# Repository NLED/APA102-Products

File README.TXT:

THERE IS NO WARRANTY FOR THE PROGRAM, TO THE EXTENT PERMITTED BY APPLICABLE LAW. 
EXCEPT WHEN OTHERWISE STATED IN WRITING THE COPYRIGHT HOLDERS AND/OR OTHER PARTIES 
PROVIDE THE PROGRAM “AS IS” WITHOUT WARRANTY OF ANY KIND, EITHER EXPRESSED OR IMPLIED,
INCLUDING, BUT NOT LIMITED TO, THE IMPLIED WARRANTIES OF MERCHANTABILITY AND FITNESS 
FOR A PARTICULAR PURPOSE. THE ENTIRE RISK AS TO THE QUALITY AND PERFORMANCE OF THE 
PROGRAM IS WITH YOU. SHOULD THE PROGRAM PROVE DEFECTIVE, YOU ASSUME THE COST OF ALL 
NECESSARY SERVICING, REPAIR OR CORRECTION.

 Original Author: Jeffrey Nygaard
 Company: Northern Lights Electronic Design, LLC
 Date: March 5, 2018
 Contact: JNygaard@NLEDshop.com
 Copyright© 2017 by Northern Lights Electronic Design, LLC. All Rights Reserved
 
;=============          www.NLEDShop.com/apa102products           ============
;=============     www.NorthernLightsElectronicDesign.com       ============

This work is licensed under a Attribution-NonCommercial 4.0 International (CC BY-NC 4.0)
https://creativecommons.org/licenses/by-nc/4.0/legalcode

Free to use for personal use, but please attribute the original author.

Commercial licenses versions are available for a donation of any amount. Contact JNygaard@NLEDshop.com for details.

================================================================================================================

Ready-made devices are available for purchase, and large batch manufacturing of any device can be requested.
Please see the webpage www.NLEDShop.com/pixelproducts

NLED is available for custom design and manufacturing, please contact via phone or email to discuss your project.

================================================================================================================

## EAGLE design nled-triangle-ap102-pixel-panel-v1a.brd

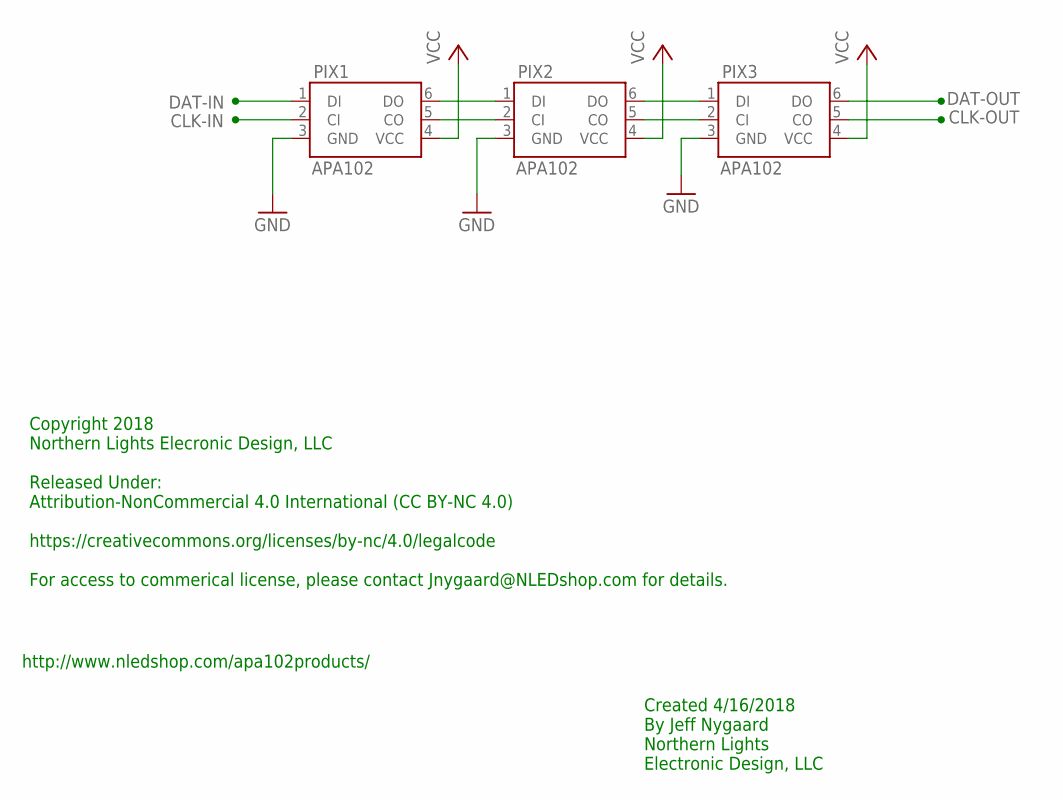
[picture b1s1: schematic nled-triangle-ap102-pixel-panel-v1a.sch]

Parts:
PIX1, PIX2, PIX3: APA102

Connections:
CLK-IN: PIX1.2 (CI)
CLK-OUT: PIX3.5 (CO)
DAT-IN: PIX1.1 (DI)
DAT-OUT: PIX3.6 (DO)
GND: PIX1.3 (GND), PIX2.3 (GND), PIX3.3 (GND)
unnamed: PIX1.6 (DO), PIX2.1 (DI)
unnamed: PIX1.5 (CO), PIX2.2 (CI)
unnamed: PIX2.6 (DO), PIX3.1 (DI)
unnamed: PIX2.5 (CO), PIX3.2 (CI)
VCC: PIX1.4 (VCC), PIX2.4 (VCC), PIX3.4 (VCC)

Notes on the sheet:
Copyright 2018 Northern Lights Elecronic Design, LLC Released Under: Attribution-NonCommercial 4.0 International (CC BY-NC 4.0) https://creativecommons.org/licenses/by-nc/4.0/legalcode For access to commerical license, please contact Jnygaard@NLEDshop.com for details.
Created 4/16/2018 By Jeff Nygaard Northern Lights Electronic Design, LLC
http://www.nledshop.com/apa102products/

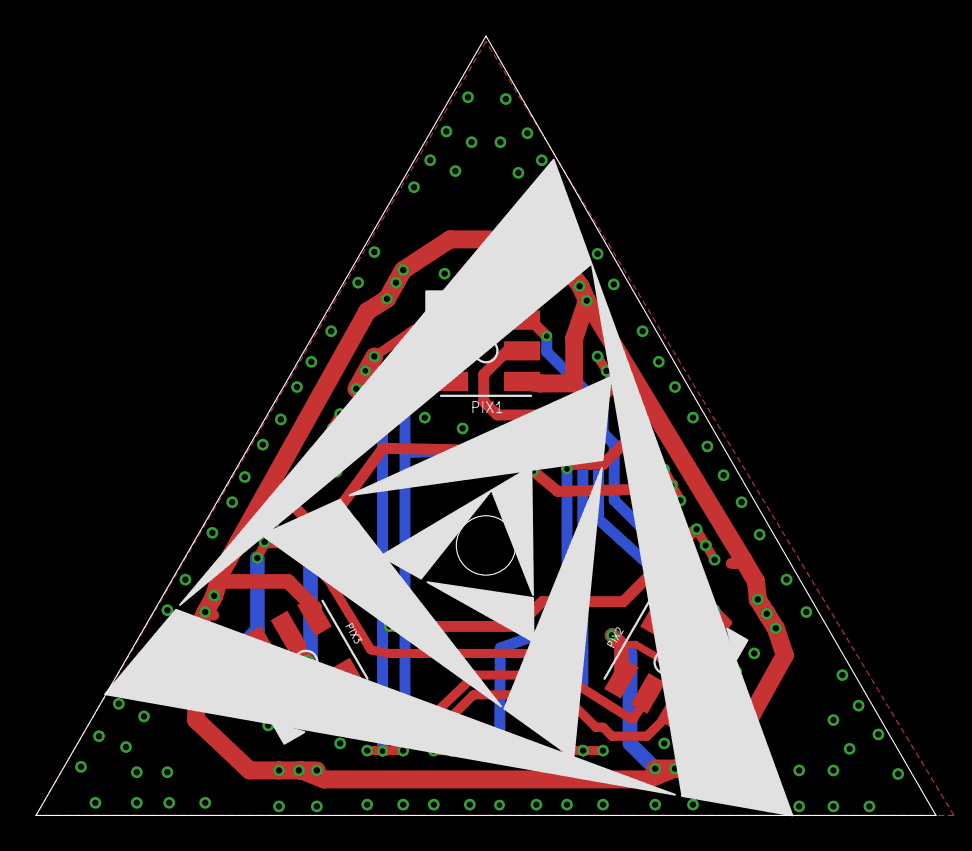
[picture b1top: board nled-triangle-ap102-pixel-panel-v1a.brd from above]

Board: 2 copper layers, 50.0 x 43.3 mm, 3 parts (0 on the bottom side), 6 nets.

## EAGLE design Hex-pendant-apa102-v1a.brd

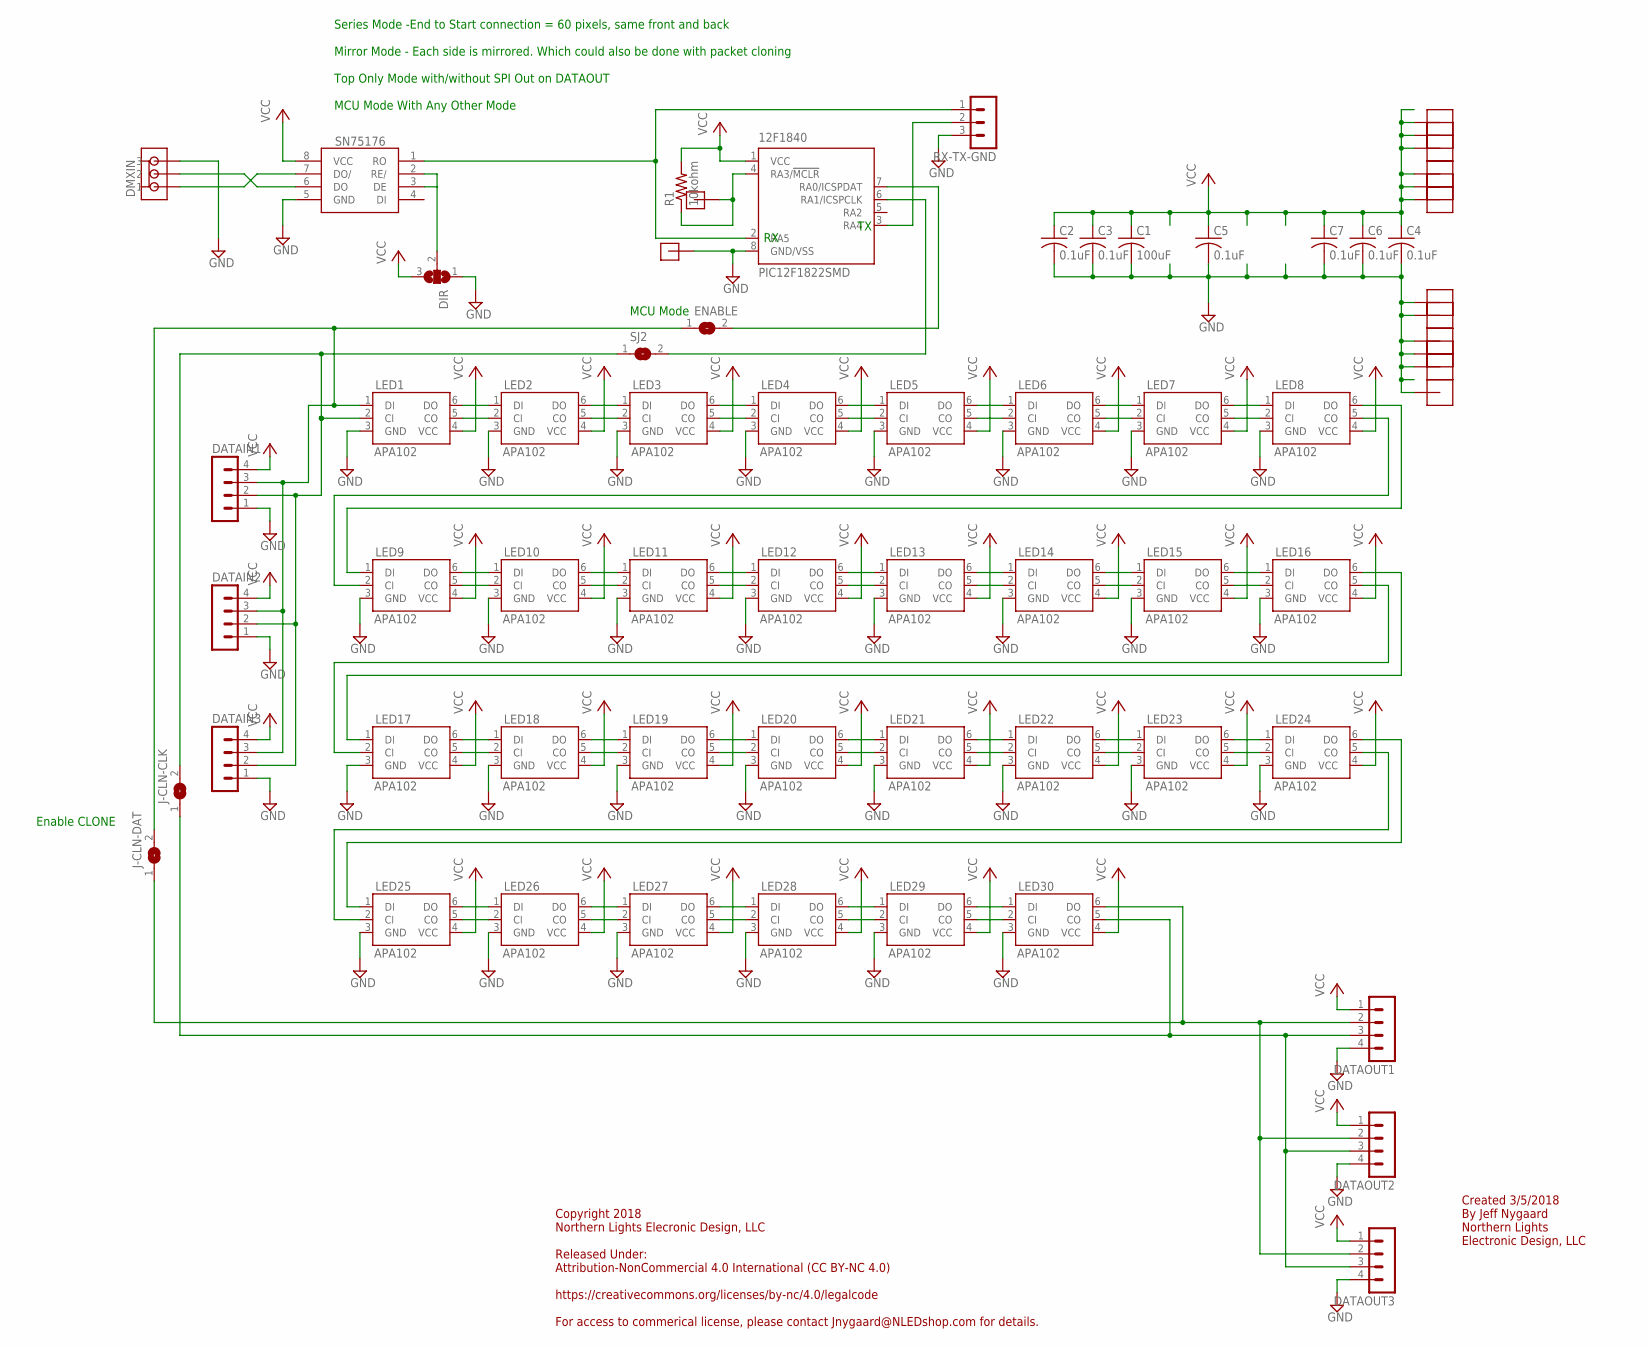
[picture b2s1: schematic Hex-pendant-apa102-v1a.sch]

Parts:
12F1840: PIC12F1822SMD; SO-08
BUTTGND: JUMPER
BUTTON: JUMPER
C1: 100uF; C1206
C2, C3, C4, C5, C6, C7: 0.1uF; C1206
DATAIN1, DATAIN2, DATAIN3: MA04-1
DATAOUT1, DATAOUT2, DATAOUT3: MA04-1
DIR: SJ2W; SJ_2
DMXIN: MOLEXKK3
ENABLE: SJ
J-CLN-CLK: SJ
J-CLN-DAT: SJ
JGND1, JGND3, JGND4, JGND5, JGND6, JGND7: 1HEADER; J1
JVCC1, JVCC2, JVCC3, JVCC4, JVCC5, JVCC6: 1HEADER; J1
LED1, LED2, LED3, LED4, LED5, LED6, LED7, LED8, LED9, LED10, LED11, LED12, LED13, LED14, LED15, LED16, LED17, LED18, LED19, LED20, LED21, LED22, LED23, LED24, LED25, LED26, LED27, LED28, LED29, LED30: APA102
R1: 10kohm; R1206
RX-TX-GND: MA03-12; MA03-1-V2
SJ2: SJ
TRANSCEIVER: SN75176SMD; SOIC-8

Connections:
GND: 12F1840.8 (GND/VSS), BUTTGND.2, C1.2, C2.2, C3.2, C4.2, C5.2, C6.2, C7.2, DATAIN1.1, DATAIN2.1, DATAIN3.1, DATAOUT1.4, DATAOUT2.4, DATAOUT3.4, DIR.1, DMXIN.3, JGND1.2, JGND3.2, JGND4.2, JGND6.2, JGND7.2, JVCC4.2, LED1.3 (GND), LED2.3 (GND), LED3.3 (GND), LED4.3 (GND), LED5.3 (GND), LED6.3 (GND), LED7.3 (GND), LED8.3 (GND), LED9.3 (GND), LED10.3 (GND), LED11.3 (GND), LED12.3 (GND), LED13.3 (GND), LED14.3 (GND), LED15.3 (GND), LED16.3 (GND), LED17.3 (GND), LED18.3 (GND), LED19.3 (GND), LED20.3 (GND), LED21.3 (GND), LED22.3 (GND), LED23.3 (GND), LED24.3 (GND), LED25.3 (GND), LED26.3 (GND), LED27.3 (GND), LED28.3 (GND), LED29.3 (GND), LED30.3 (GND), RX-TX-GND.3, TRANSCEIVER.5 (GND)
unnamed: LED1.6 (DO), LED2.1 (DI)
unnamed: LED2.6 (DO), LED3.1 (DI)
unnamed: LED3.6 (DO), LED4.1 (DI)
unnamed: LED3.5 (CO), LED4.2 (CI)
unnamed: LED2.5 (CO), LED3.2 (CI)
unnamed: LED1.5 (CO), LED2.2 (CI)
unnamed: LED4.6 (DO), LED5.1 (DI)
unnamed: LED4.5 (CO), LED5.2 (CI)
unnamed: LED5.6 (DO), LED6.1 (DI)
unnamed: LED5.5 (CO), LED6.2 (CI)
unnamed: LED8.5 (CO), LED9.2 (CI)
unnamed: LED8.6 (DO), LED9.1 (DI)
unnamed: LED7.6 (DO), LED8.1 (DI)
unnamed: LED7.5 (CO), LED8.2 (CI)
unnamed: LED6.5 (CO), LED7.2 (CI)
unnamed: LED6.6 (DO), LED7.1 (DI)
unnamed: LED17.6 (DO), LED18.1 (DI)
unnamed: LED18.6 (DO), LED19.1 (DI)
unnamed: LED19.6 (DO), LED20.1 (DI)
unnamed: LED19.5 (CO), LED20.2 (CI)
unnamed: LED18.5 (CO), LED19.2 (CI)
unnamed: LED9.6 (DO), LED10.1 (DI)
unnamed: LED10.6 (DO), LED11.1 (DI)
unnamed: LED11.6 (DO), LED12.1 (DI)
unnamed: LED11.5 (CO), LED12.2 (CI)
unnamed: LED10.5 (CO), LED11.2 (CI)
unnamed: LED9.5 (CO), LED10.2 (CI)
unnamed: LED12.6 (DO), LED13.1 (DI)
unnamed: LED12.5 (CO), LED13.2 (CI)
unnamed: LED13.6 (DO), LED14.1 (DI)
unnamed: LED13.5 (CO), LED14.2 (CI)
unnamed: LED14.6 (DO), LED15.1 (DI)
unnamed: LED14.5 (CO), LED15.2 (CI)
unnamed: LED15.6 (DO), LED16.1 (DI)
unnamed: LED15.5 (CO), LED16.2 (CI)
unnamed: LED17.5 (CO), LED18.2 (CI)
unnamed: LED20.6 (DO), LED21.1 (DI)
unnamed: LED20.5 (CO), LED21.2 (CI)
unnamed: LED21.6 (DO), LED22.1 (DI)
unnamed: LED21.5 (CO), LED22.2 (CI)
unnamed: LED25.6 (DO), LED26.1 (DI)
unnamed: LED26.6 (DO), LED27.1 (DI)
unnamed: LED27.6 (DO), LED28.1 (DI)
unnamed: LED27.5 (CO), LED28.2 (CI)
unnamed: LED26.5 (CO), LED27.2 (CI)
unnamed: LED25.5 (CO), LED26.2 (CI)
unnamed: LED28.6 (DO), LED29.1 (DI)
unnamed: LED28.5 (CO), LED29.2 (CI)
unnamed: LED29.6 (DO), LED30.1 (DI)
unnamed: LED29.5 (CO), LED30.2 (CI)
unnamed: LED24.5 (CO), LED25.2 (CI)
unnamed: LED24.6 (DO), LED25.1 (DI)
unnamed: LED23.6 (DO), LED24.1 (DI)
unnamed: LED23.5 (CO), LED24.2 (CI)
unnamed: LED22.5 (CO), LED23.2 (CI)
unnamed: LED22.6 (DO), LED23.1 (DI)
unnamed: LED16.5 (CO), LED17.2 (CI)
unnamed: LED16.6 (DO), LED17.1 (DI)
unnamed: DATAIN1.3, DATAIN2.3, DATAIN3.3, ENABLE.1, J-CLN-DAT.2, LED1.1 (DI)
unnamed: DATAIN1.2, DATAIN2.2, DATAIN3.2, J-CLN-CLK.2, LED1.2 (CI), SJ2.1
unnamed: DATAOUT1.3, DATAOUT2.3, DATAOUT3.3, J-CLN-CLK.1, LED30.5 (CO)
unnamed: DATAOUT1.2, DATAOUT2.2, DATAOUT3.2, J-CLN-DAT.1, LED30.6 (DO)
unnamed: 12F1840.2 (RA5), RX-TX-GND.1, TRANSCEIVER.1 (RO)
unnamed: DIR.2, TRANSCEIVER.2 (RE/), TRANSCEIVER.3 (DE)
unnamed: 12F1840.4 (RA3/!MCLR), BUTTON.2, R1.1
unnamed: DMXIN.2, TRANSCEIVER.6 (DO)
unnamed: 12F1840.3 (RA4), RX-TX-GND.2
unnamed: DMXIN.1, TRANSCEIVER.7 (DO/)
unnamed: 12F1840.7 (RA0/ICSPDAT), ENABLE.2
unnamed: 12F1840.6 (RA1/ICSPCLK), SJ2.2
VCC: 12F1840.1 (VCC), C1.1, C2.1, C3.1, C4.1, C5.1, C6.1, C7.1, DATAIN1.4, DATAIN2.4, DATAIN3.4, DATAOUT1.1, DATAOUT2.1, DATAOUT3.1, DIR.3, JGND5.2, JVCC1.2, JVCC2.2, JVCC3.2, JVCC5.2, JVCC6.2, LED1.4 (VCC), LED2.4 (VCC), LED3.4 (VCC), LED4.4 (VCC), LED5.4 (VCC), LED6.4 (VCC), LED7.4 (VCC), LED8.4 (VCC), LED9.4 (VCC), LED10.4 (VCC), LED11.4 (VCC), LED12.4 (VCC), LED13.4 (VCC), LED14.4 (VCC), LED15.4 (VCC), LED16.4 (VCC), LED17.4 (VCC), LED18.4 (VCC), LED19.4 (VCC), LED20.4 (VCC), LED21.4 (VCC), LED22.4 (VCC), LED23.4 (VCC), LED24.4 (VCC), LED25.4 (VCC), LED26.4 (VCC), LED27.4 (VCC), LED28.4 (VCC), LED29.4 (VCC), LED30.4 (VCC), R1.2, TRANSCEIVER.8 (VCC)

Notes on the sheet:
Series Mode -End to Start connection = 60 pixels, same front and back Mirror Mode - Each side is mirrored. Which could also be done with packet cloning Top Only Mode with/without SPI Out on DATAOUT MCU Mode With Any Other Mode
Enable CLONE
MCU Mode
Copyright 2018 Northern Lights Elecronic Design, LLC Released Under: Attribution-NonCommercial 4.0 International (CC BY-NC 4.0) https://creativecommons.org/licenses/by-nc/4.0/legalcode For access to commerical license, please contact Jnygaard@NLEDshop.com for details.
Created 3/5/2018 By Jeff Nygaard Northern Lights Electronic Design, LLC

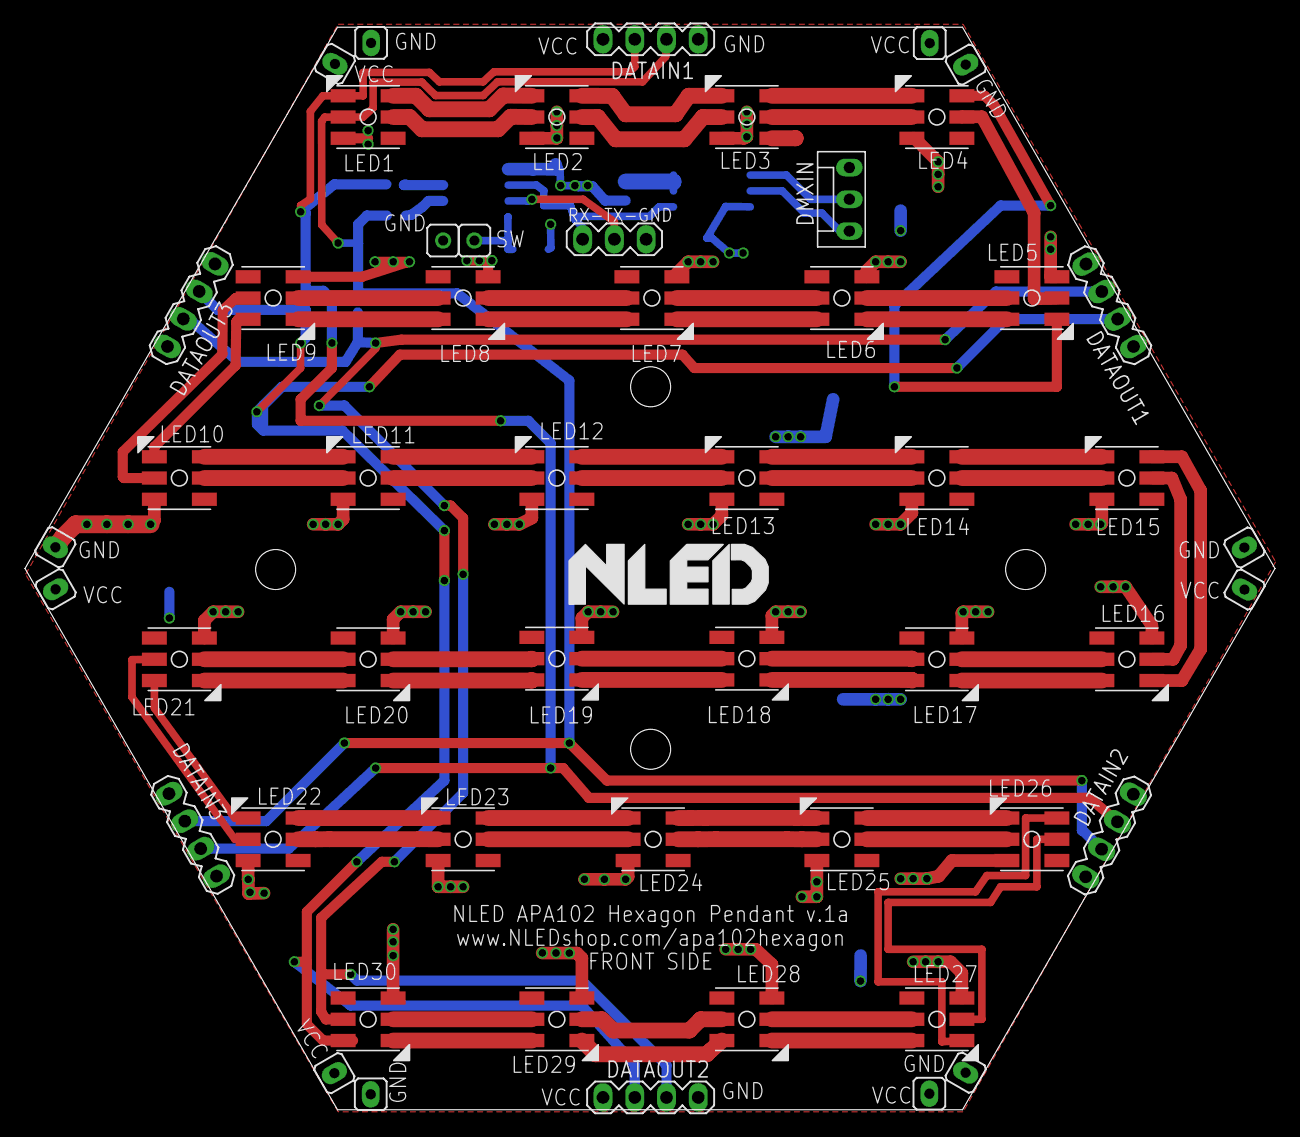
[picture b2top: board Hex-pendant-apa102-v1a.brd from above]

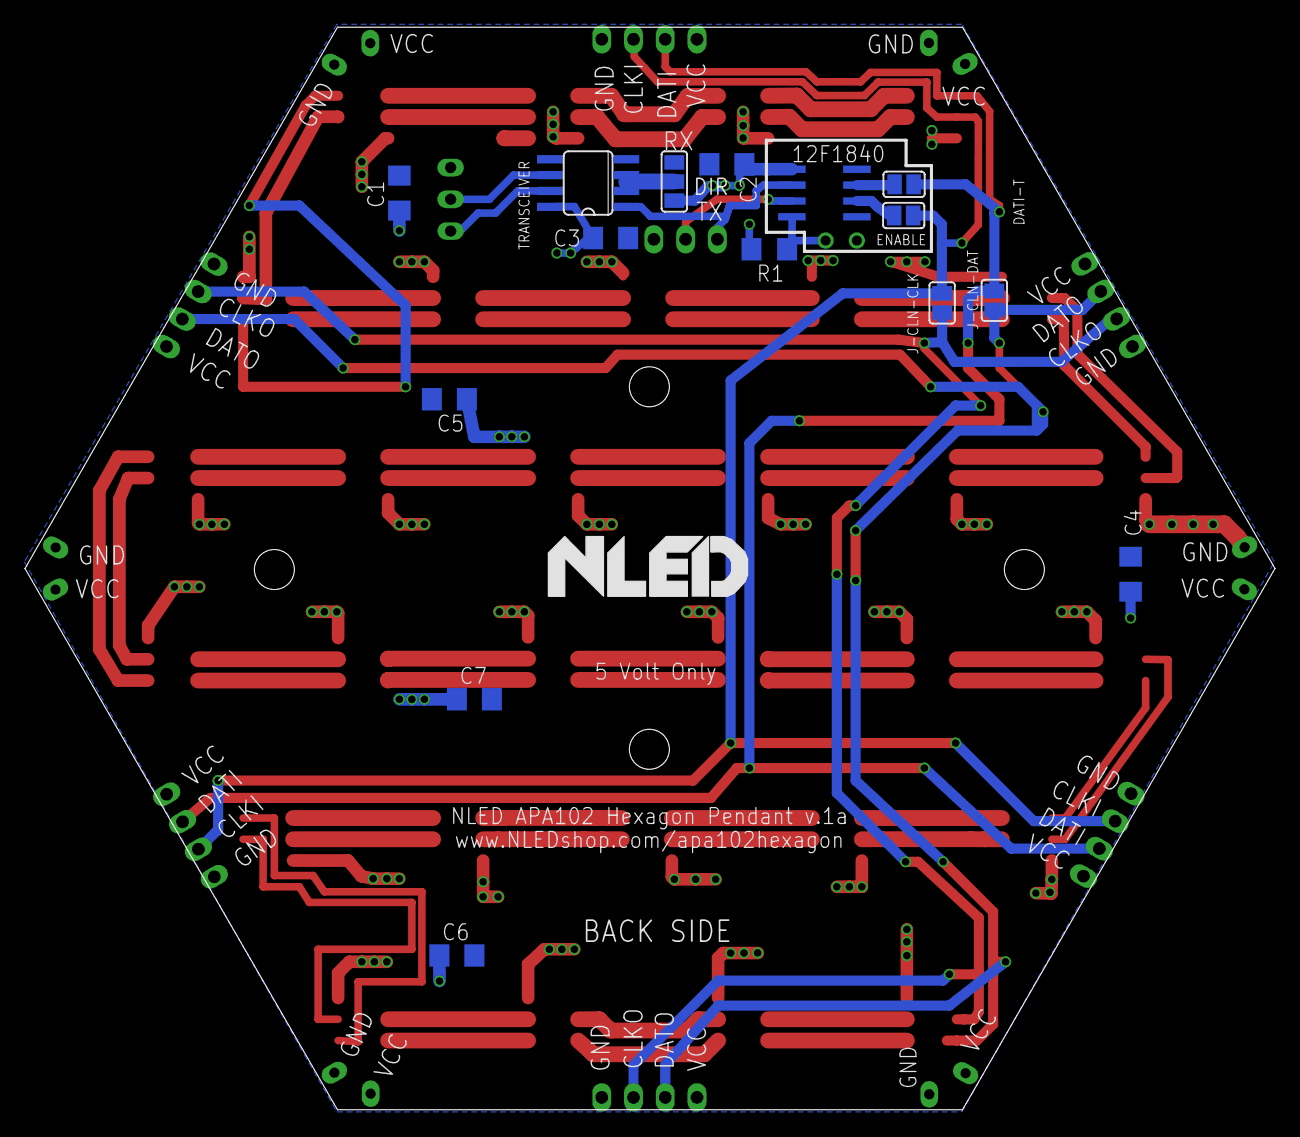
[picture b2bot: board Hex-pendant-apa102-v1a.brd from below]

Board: 2 copper layers, 100.0 x 86.6 mm, 67 parts (15 on the bottom side), 72 nets.
